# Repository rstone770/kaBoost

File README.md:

kaBoost
=======

Ultra simple boost circuit.

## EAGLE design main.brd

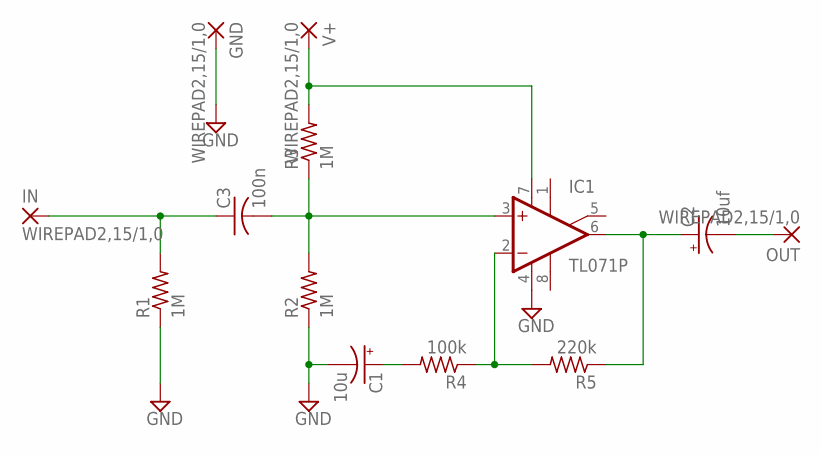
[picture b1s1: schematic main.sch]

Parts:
C1: 10u; PANASONIC_C
C2: 10uf; PANASONIC_C
C3: 100n; C0805
GND: WIREPAD2,15/1,0; 2,15/1,0
IC1: TL071P; DIL08
IN: WIREPAD2,15/1,0; 2,15/1,0
OUT: WIREPAD2,15/1,0; 2,15/1,0
R1, R2, R3: 1M; R0805
R4: 100k; R0805
R5: 220k; R0805
V+: WIREPAD2,15/1,0; 2,15/1,0

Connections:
GND: C1.-, GND.1, IC1.4 (V-), R1.1, R2.1
unnamed: C3.2, IC1.3 (+IN), R2.2, R3.1
unnamed: C2.-, OUT.1
unnamed: C1.+, R4.2
unnamed: IC1.2 (-IN), R4.1, R5.2
unnamed: C2.+, IC1.6 (OUT), R5.1
unnamed: IC1.7 (V+), R3.2, V+.1
unnamed: C3.1, IN.1, R1.2

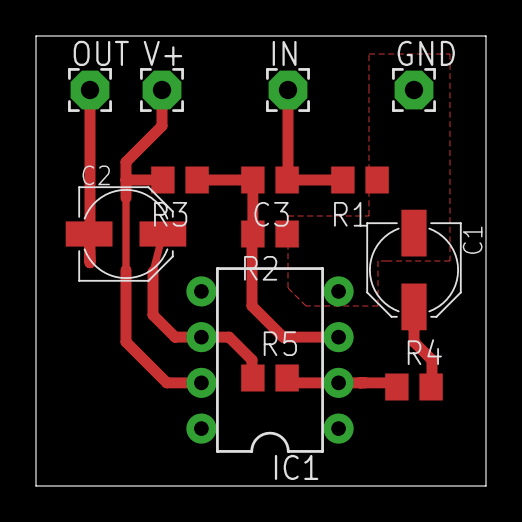
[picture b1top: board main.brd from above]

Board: 2 copper layers, 25.0 x 25.0 mm, 13 parts (0 on the bottom side), 8 nets.

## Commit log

2017-03-04 Initial commit.
2017-03-04 Remove extraneous libraries.
2017-03-04 Ignore autosave.
2017-04-12 Convert to smd.
2017-04-12 Clean up traces.
2017-04-12 Add ground fill.
2017-04-15 Add more clearance between cap and a dip socket.
